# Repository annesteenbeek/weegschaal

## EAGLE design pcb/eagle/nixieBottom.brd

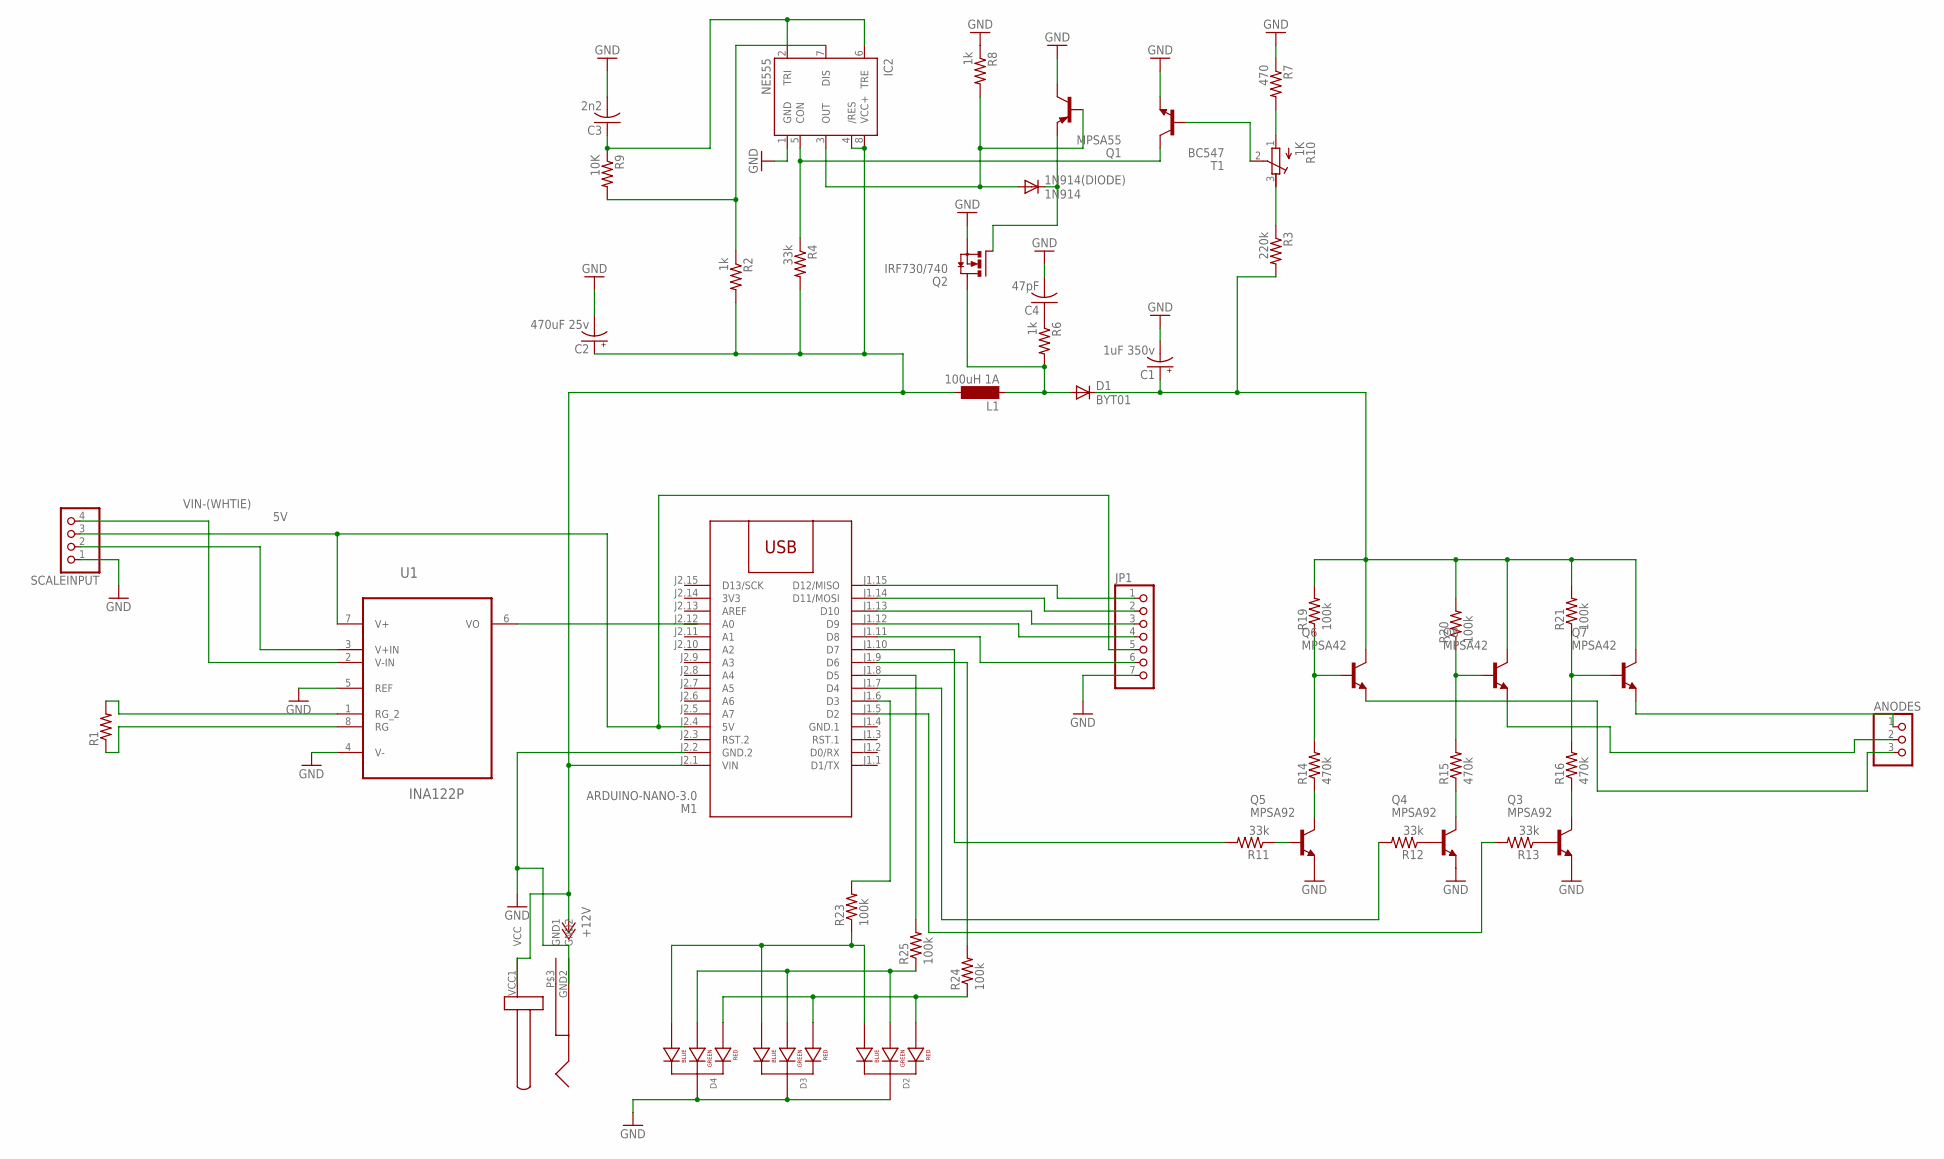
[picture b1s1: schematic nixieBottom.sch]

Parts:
1N914(DIODE): 1N914; DO35-10
ANODES: PINHD-1X3; 1X03
C1: 1uF 350v; E2,5-7
C2: 470uF 25v; E5-10,5
C3: 2n2; C050-024X044
C4: 47pF; C075-032X103
D1: BYT01; F126-10
D2, D3, D4: LED-RGB-CC-THRUCLEAR; LED-RGB-THRU
IC2: NE555; DIL-08
JP1: PINHD-1X7; 1X07
L1: 100uH 1A; SD75
M1: ARDUINO-NANO-3.0
Q1: MPSA55; TO92-CBE
Q2: IRF730/740; TO220BH
Q3, Q4, Q5: MPSA92; TO92
Q6, Q7, Q8: MPSA42; TO92
R1: R-US_0204/2V; 0204V
R2, R6, R8: 1k; 0207/2V
R3: 220k; 0207/2V
R4, R11, R12, R13: 33k; 0207/2V
R7: 470; 0207/2V
R9: 10K; 0207/2V
R10: 1K; RTRIM3339P
R14, R15, R16: 470k; 0207/2V
R19, R20, R21, R23, R24, R25: 100k; 0207/2V
SCALEINPUT: PINHD-1X4; 1X04
T1: BC547; TO92
U1: INA122P; DIP254P762X508-8
U$1: CONNECTOR

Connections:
3V3: M1.J2.14 (3V3)
5V: JP1.5, M1.J2.4 (5V), SCALEINPUT.3, U1.7 (V+)
+12V: C2.+, IC2.4 (/RES), IC2.8 (VCC+), L1.2, M1.J2.1 (VIN), R2.2, R4.2, U$1.VCC1 (VCC)
GND: C1.-, C2.-, C3.2, C4.2, D2.2 (CATHODE), D3.2 (CATHODE), D4.2 (CATHODE), IC2.1 (GND), JP1.7, M1.J2.2 (GND.2), Q1.C, Q2.S, Q3.3 (E), Q4.3 (E), Q5.3 (E), R7.1, R8.1, SCALEINPUT.1, T1.1 (E), U1.4 (V-), U1.5 (REF), U$1.GND2
GND.1: M1.J1.4 (GND.1)
unnamed: R1.2, U1.1 (RG_2)
unnamed: JP1.6, M1.J1.11 (D8)
unnamed: R1.1, U1.8 (RG)
unnamed: SCALEINPUT.2, U1.3 (V+IN)
unnamed: M1.J1.6 (D3), R23.2
unnamed: M1.J1.9 (D6), R24.2
unnamed: M1.J1.8 (D5), R25.2
unnamed: JP1.1, M1.J1.15 (D12/MISO)
unnamed: JP1.2, M1.J1.14 (D11/MOSI)
unnamed: JP1.3, M1.J1.13 (D10)
unnamed: JP1.4, M1.J1.12 (D9)
unnamed: C3.1, IC2.2 (TRI), IC2.6 (TRE), R9.1
unnamed: IC2.7 (DIS), R2.1, R9.2
unnamed: Q5.1 (B), R11.1
unnamed: IC2.5 (CON), R4.1, T1.3 (C)
unnamed: R7.2, R10.1 (E)
unnamed: R10.2 (S), T1.2 (B)
unnamed: R3.1, R10.3 (A)
unnamed: C4.1, R6.1
unnamed: 1N914(DIODE).A, IC2.3 (OUT), Q1.B, R8.2
unnamed: 1N914(DIODE).C, Q1.E, Q2.G
unnamed: D1.A, L1.1, Q2.D, R6.2
unnamed: C1.+, D1.C, Q6.2 (C), Q7.2 (C), Q8.2 (C), R3.2, R19.2, R20.2, R21.2
unnamed: Q4.1 (B), R12.1
unnamed: Q3.1 (B), R13.1
unnamed: M1.J1.10 (D7), R11.2
unnamed: M1.J1.7 (D4), R12.2
unnamed: M1.J1.5 (D2), R13.2
unnamed: Q6.1 (B), R14.2, R19.1
unnamed: Q8.1 (B), R15.2, R20.1
unnamed: Q7.1 (B), R16.2, R21.1
unnamed: Q3.2 (C), R16.1
unnamed: Q4.2 (C), R15.1
unnamed: Q5.2 (C), R14.1
unnamed: ANODES.1, Q7.3 (E)
unnamed: ANODES.2, Q8.3 (E)
unnamed: ANODES.3, Q6.3 (E)
unnamed: D2.4 (BLUE_CATHODE), D3.4 (BLUE_CATHODE), D4.4 (BLUE_CATHODE), R23.1
unnamed: D2.3 (GREEN_CATHODE), D3.3 (GREEN_CATHODE), D4.3 (GREEN_CATHODE), R25.1
unnamed: D2.1 (RED_CATHODE), D3.1 (RED_CATHODE), D4.1 (RED_CATHODE), R24.1
VIN-(WHTIE): SCALEINPUT.4, U1.2 (V-IN)

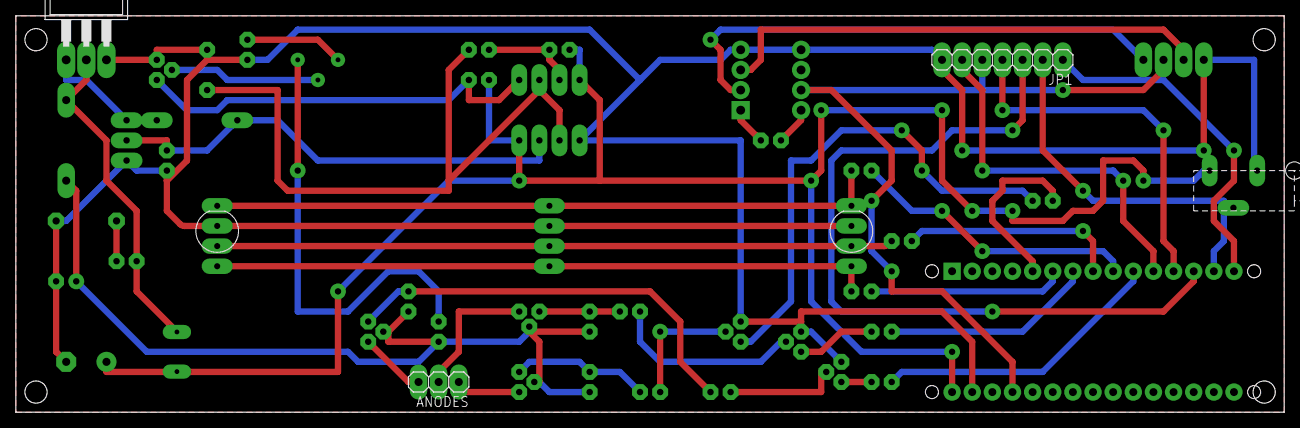
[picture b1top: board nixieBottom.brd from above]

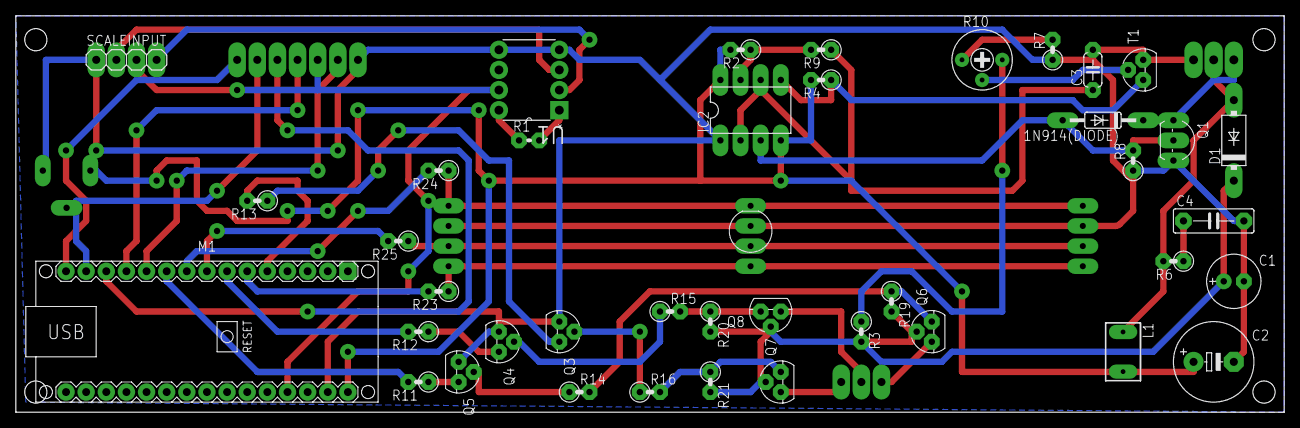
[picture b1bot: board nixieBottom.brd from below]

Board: 2 copper layers, 160.0 x 50.0 mm, 47 parts (41 on the bottom side), 44 nets.

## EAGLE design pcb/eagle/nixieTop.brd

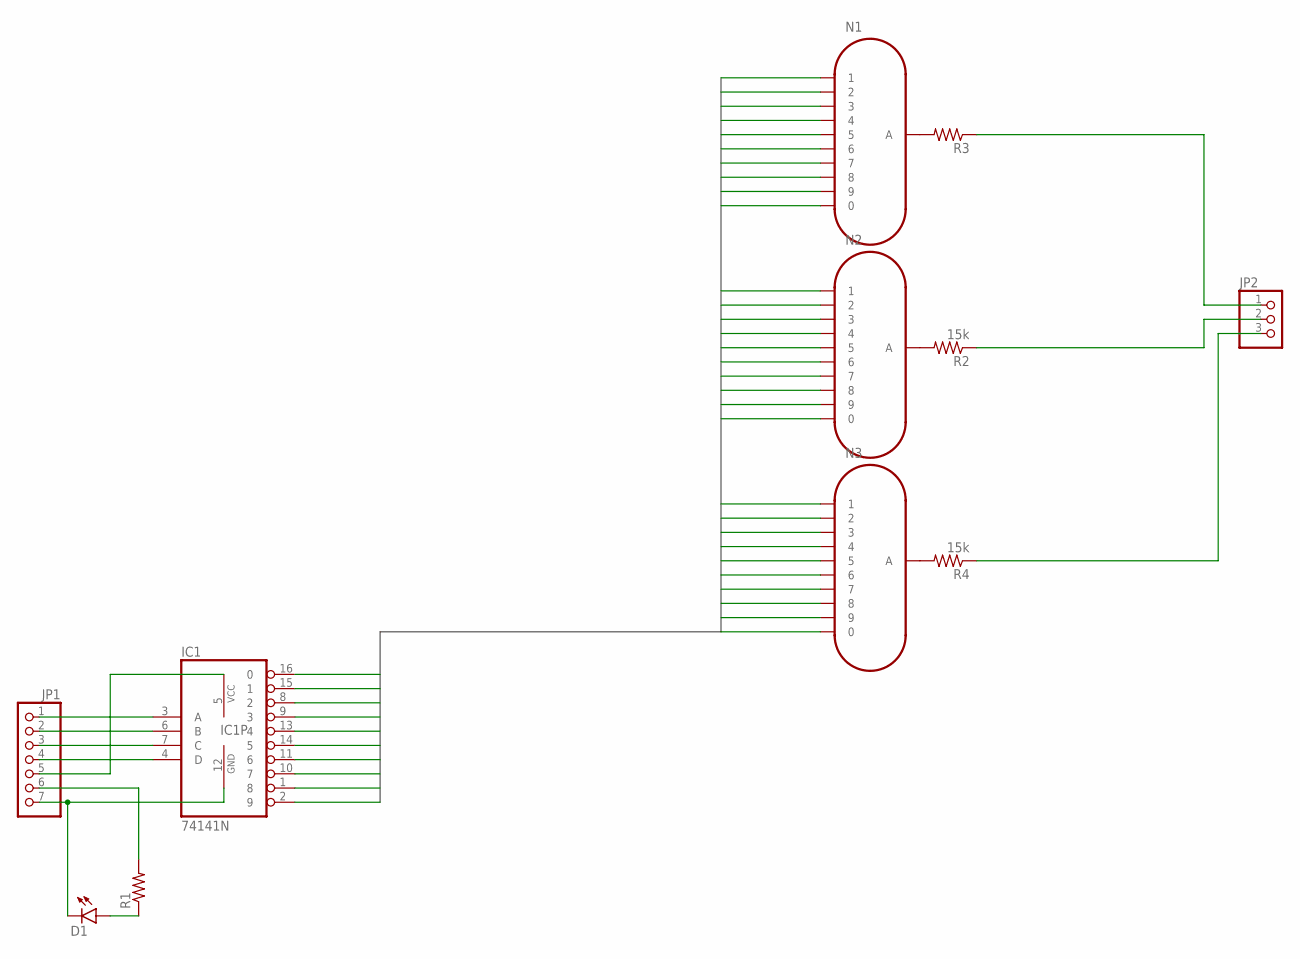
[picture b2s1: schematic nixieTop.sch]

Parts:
D1: LED5MM
IC1: 74141N; DIL16
JP1: PINHD-1X7; 1X07
JP2: PINHD-1X3; 1X03
N1, N2, N3: IN-4; IN-18
R1, R3: R-US_0204/2V; 0204V
R2, R4: 15k; 0204V

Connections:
D0: IC1.16 (0), N1.8 (0), N2.8 (0), N3.8 (0)
D1: IC1.15 (1), N1.14 (1), N2.14 (1), N3.14 (1)
D2: IC1.8 (2), N1.9 (2), N2.9 (2), N3.9 (2)
D3: IC1.9 (3), N1.11 (3), N2.11 (3), N3.11 (3)
D4: IC1.13 (4), N1.1 (4), N2.1 (4), N3.1 (4)
D5: IC1.14 (5), N1.12 (5), N2.12 (5), N3.12 (5)
D6: IC1.11 (6), N1.2 (6), N2.2 (6), N3.2 (6)
D7: IC1.10 (7), N1.6 (7), N2.6 (7), N3.6 (7)
D8: IC1.1 (8), N1.3 (8), N2.3 (8), N3.3 (8)
D9: IC1.2 (9), N1.5 (9), N2.5 (9), N3.5 (9)
unnamed: D1.A, R1.1
unnamed: JP1.6, R1.2
unnamed: JP2.3, R4.1
unnamed: N1.4 (A), R3.2
unnamed: JP2.2, R2.1
unnamed: JP2.1, R3.1
unnamed: N2.4 (A), R2.2
unnamed: N3.4 (A), R4.2
unnamed: IC1.3 (A), JP1.1
unnamed: IC1.6 (B), JP1.2
unnamed: IC1.7 (C), JP1.3
unnamed: IC1.4 (D), JP1.4
unnamed: IC1.5 (VCC), JP1.5
unnamed: D1.K (C), IC1.12 (GND), JP1.7

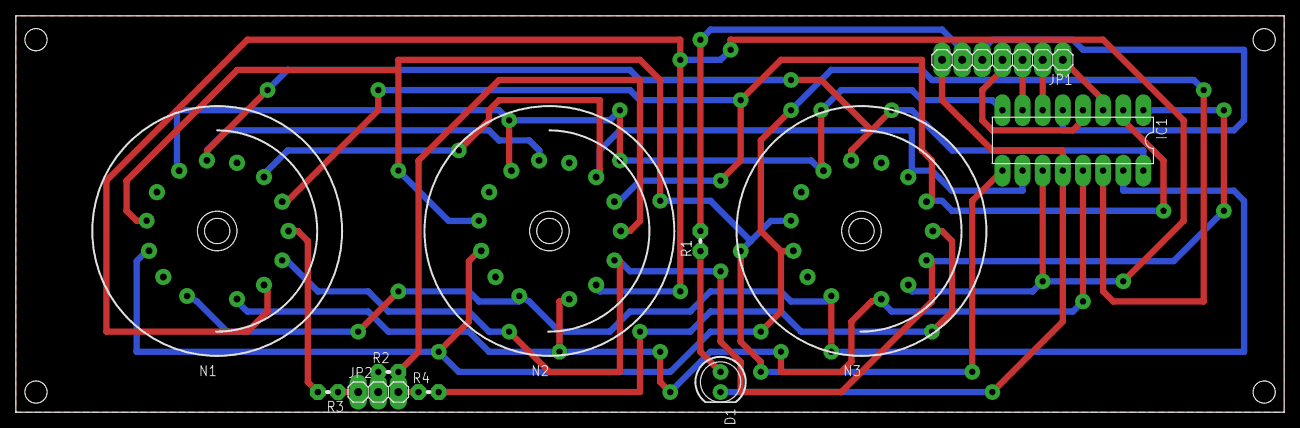
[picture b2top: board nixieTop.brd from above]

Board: 2 copper layers, 160.0 x 50.0 mm, 11 parts (0 on the bottom side), 24 nets.

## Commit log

2014-07-30 weegschaal
2014-07-30 begin ijkprocedure ingebouwd
    bla
2014-07-30 Kijk er even naar, help!
2014-07-30 nog een keer
2014-07-30 dit is nieuw
2014-07-30 alles opgelost met git
2014-08-01 Goede mapfunctie
2014-08-02 float map functie ingebouwd
    de map-functie heb ik vervangen door een map-functie die float gebruikt
2014-08-02 hanmatige reset ingebouwd
    als je reset intypt in de serial viewer dan wordt het startvoltage
    opnieuw berekend.
    Om de zoveel tijd reset hij zichzelf spontaan. Ben er nog niet achter
    waarom dat precies gebeurt...
2014-08-17 Terug naar laatste Edit
2014-09-14 Save functionaliteit toegevoegd communicatie met arduino toegevoegd recursieve updates toegevoegd
2014-09-14 De code opgeschoond en nixie code toegevoegd, het mappen gebeurt nu met rouwe sensor data.
2014-09-14 datasheets van de shiftregisters en de BSD->DEC chips
2014-09-14 minor fixes
2014-09-19 added start sensor value for scale
2014-09-23 fixed nixie issue
2014-09-26 Gemiddeld voltage ingebouwd
    Berekent nu het gemiddelde voltage over 50 meetwaarden.
2014-09-26 Startgewicht kan gekozen worden
    In plaats van 0 kan nu ook een ander startgewicht ingevoerd worden, voor
    betere calibratie.
2014-09-26 delay van 1 sec
2014-10-16 some line errors and syntax fixees
2014-11-26 repaired arduino code, organized git
2014-11-26 added communication with indicator
2014-11-26 added to do
2014-12-21 cleaned up code, working on serial com
2014-12-21 still working on serial communication
2014-12-21 added call function while in main for communication
2014-12-28 removed ledson, improved accuracy of emptyweight
2014-12-30 commit before branching
2014-12-30 added test text
2015-01-03 Timeout arduino readings
2015-01-05 working communication, and load save functionality
2015-07-10 cleaned up directory, added pcb
2015-07-21 cleaned up directory, added pcb designs
2015-07-21 removed pcb sketch files
2015-07-21 added pcb projects
2015-07-22 setnum function, cleaned up code
2015-07-22 added RGB function and hex conversion, added waits to multiplexing
2015-07-22 removed pcb from git
2015-07-22 restructure
2015-07-25 cleaned up code
2015-07-25 changed wait function to delaymicroseconds
2015-07-25 small code cleanups
2015-07-26 added serial port selector
2015-07-26 added color selection dialog
2015-07-26 added variables to class and removed globals
2015-07-26 changed save system to json
2015-07-26 improved serial selection and color picker
2015-07-26 function name change
2015-07-28 working, but no good save function
2015-07-28 added fustlijst changes
2015-07-28 added varname dict
2015-07-28 adding usb dict
2015-07-28 added dict for usb
2015-07-29 correct color selection dialog and printing
2015-07-29 small changes
2015-07-31 modified arduino code to match communication
2015-08-02 added calibration interface
2015-08-02 fixed icon directory problem
2015-08-02 added calibration to arduino code

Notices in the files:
parts and their libraries:
diy-modules: Released under the Creative Commons Attribution 4.0 International License: http://creativecommons.org/licenses/by/4.0
SparkFun-LED: Licensing: Creative Commons ShareAlike 4.0 International - https://creativecommons.org/licenses/by-sa/4.0
